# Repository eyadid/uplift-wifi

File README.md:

# uplift-wifi 
Details and project logs are available on [Hackaday.io](http://hackaday.io/project/4173-uplift-desk-wifi-link)

Schematics files created with [EAGLECAD](http://www.cadsoftusa.com/download-eagle/)

LUA code is written for ESP8266 running the latest [NODEMCU](https://github.com/nodemcu/nodemcu-firmware)

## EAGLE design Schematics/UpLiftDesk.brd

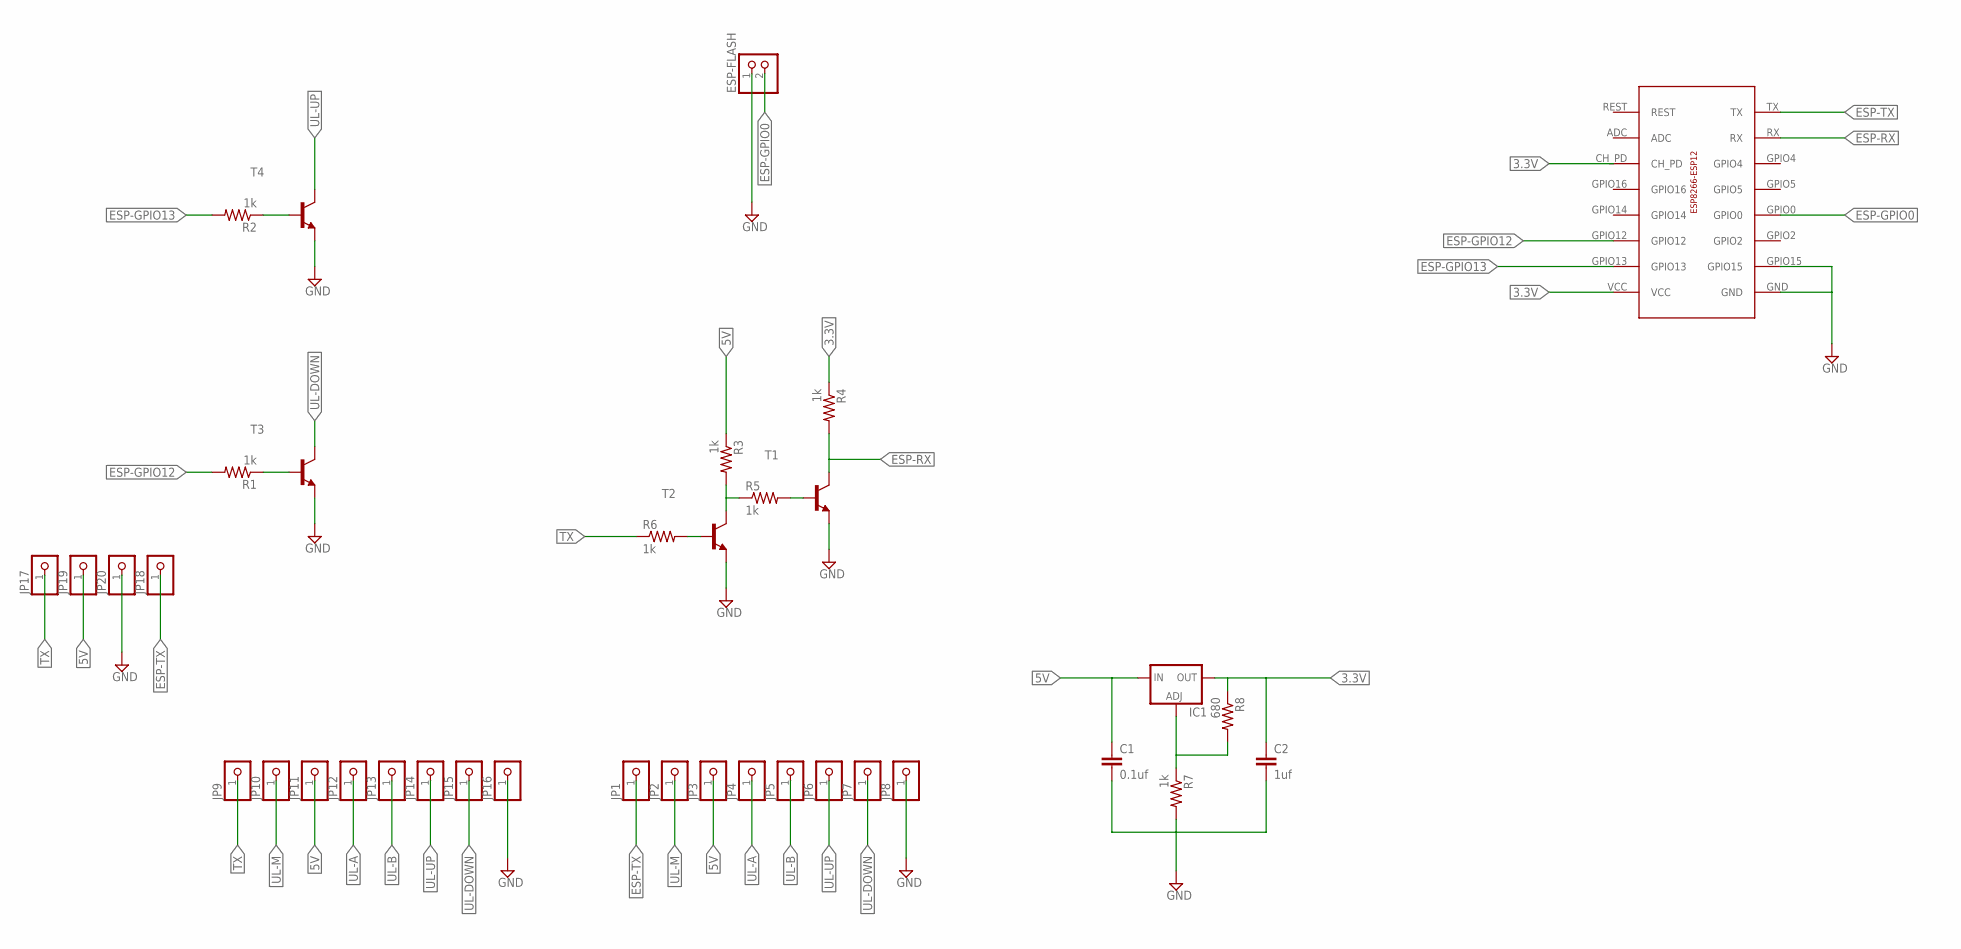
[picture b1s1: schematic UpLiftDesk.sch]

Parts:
C1: 0.1uf; C2.5-2
C2: 1uf; C2.5-2
ESP-FLASH: PINHD-1X2; 1X02
IC1: LM317TS; 317TS
JP1, JP2, JP3, JP4, JP5, JP6, JP7, JP8, JP9, JP10, JP11, JP12, JP13, JP14, JP15, JP16, JP17, JP18, JP19, JP20: PINHD-1X1; 1X01
R1, R2, R3, R4, R5, R6, R7: 1k; 0204/7
R8: 680; 0204/7
T1, T2, T3, T4: -NPN-TO92-EBC; TO92-EBC
U$2: ESP-12-THROUGH

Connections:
3.3V: C2.1, IC1.2 (OUT), R4.1, R8.1, U$2.CH_PD, U$2.VCC
5V: C1.1, IC1.3 (IN), JP3.1, JP11.1, JP19.1, R3.1
ESP-GPIO0: ESP-FLASH.2, U$2.GPIO0
ESP-GPIO12: R1.2, U$2.GPIO12
ESP-GPIO13: R2.2, U$2.GPIO13
ESP-RX: R4.2, T1.C, U$2.RX
ESP-TX: JP1.1, JP18.1, U$2.TX
GND: C1.2, C2.2, ESP-FLASH.1, JP8.1, JP16.1, JP20.1, R7.2, T1.E, T2.E, T3.E, T4.E, U$2.GND, U$2.GPIO15
unnamed: R3.2, R5.1, T2.C
unnamed: R6.2, T2.B
unnamed: R1.1, T3.B
unnamed: R2.1, T4.B
unnamed: R5.2, T1.B
unnamed: IC1.1 (ADJ), R7.1, R8.2
TX: JP9.1, JP17.1, R6.1
UL-A: JP4.1, JP12.1
UL-B: JP5.1, JP13.1
UL-DOWN: JP7.1, JP15.1, T3.C
UL-M: JP2.1, JP10.1
UL-UP: JP6.1, JP14.1, T4.C

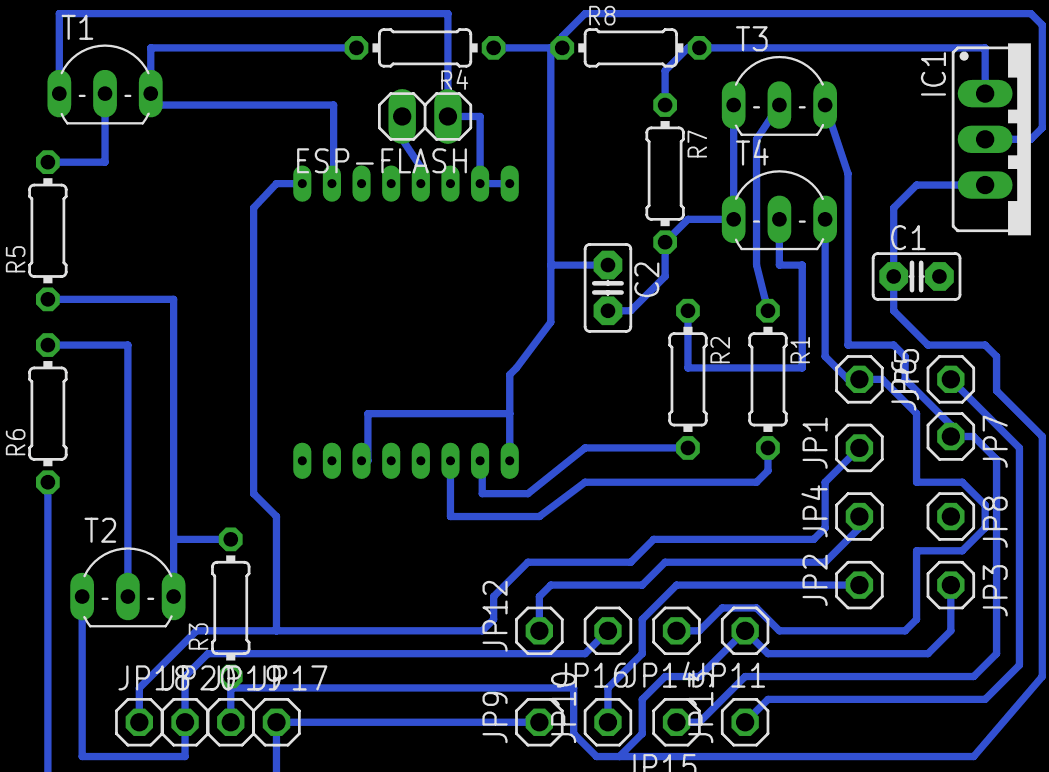
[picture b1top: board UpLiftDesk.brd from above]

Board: 2 copper layers, 37 parts (1 on the bottom side), 20 nets.

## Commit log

2015-02-04 Modify readme - add link to Hackaday.io
2015-02-04 More readme updates
2015-02-06 Change ESP to through hole
